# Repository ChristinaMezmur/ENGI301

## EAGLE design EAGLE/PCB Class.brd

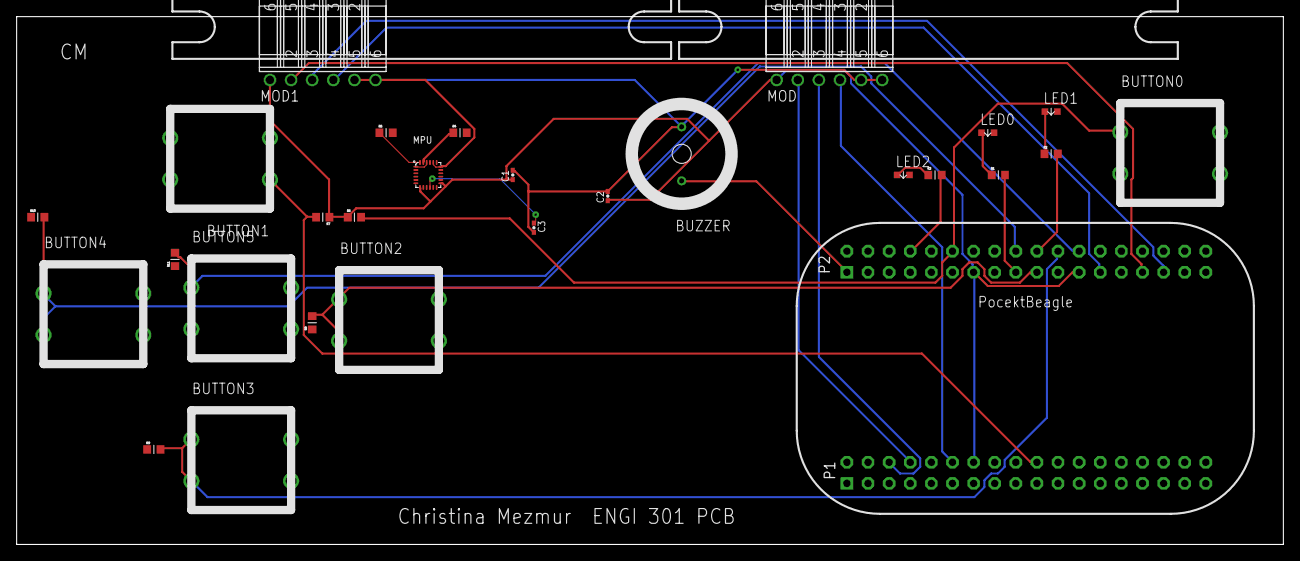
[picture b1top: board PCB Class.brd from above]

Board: 4 copper layers, 152.4 x 63.5 mm, 32 parts (0 on the bottom side), 30 nets.

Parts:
BUTTON0, BUTTON1, BUTTON2, BUTTON3, BUTTON4, BUTTON5: BUTTON
BUZZER: SEM-1203(42)
C1: 10nF; C0402
C2, C3: 0.1uF; C0402
LED0, LED1, LED2: LTST-C191TBKT
MOD, MOD1: MOD-LED8X8RGB-CONN; FE06W
MPU: QFN-3MMX3MM
POCKETBEAGLE: POCKETBEAGLE
R1, R2, R3: 1K; R0603
R4, R5, R6, R7, R8, R9, R10, R11: 3K; R0603
U$1, U$2, U$3, U$4: MOD-LED8X8RGB

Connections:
8X8CLK: MOD.2, POCKETBEAGLE.8
8X8CLK1: MOD1.2, POCKETBEAGLE.65
8X8CS: MOD.3, POCKETBEAGLE.6
8X8CS1: MOD1.3, POCKETBEAGLE.67
8X8MOSI: MOD.4, POCKETBEAGLE.12
8X8MOSI1: MOD1.4, POCKETBEAGLE.61
BUTTON0: BUTTON0.P$1, BUTTON0.P$3, POCKETBEAGLE.48, R6.2
BUTTON1: BUTTON1.P$1, BUTTON1.P$3, POCKETBEAGLE.20, R7.2
BUTTON2: BUTTON2.P$1, BUTTON2.P$3, POCKETBEAGLE.55, R8.2
BUTTON3: BUTTON3.P$1, BUTTON3.P$3, POCKETBEAGLE.58, R9.2
BUTTON4: BUTTON4.P$1, BUTTON4.P$3, POCKETBEAGLE.54, R10.2
BUTTON5: BUTTON5.P$1, BUTTON5.P$3, POCKETBEAGLE.60, R11.2
GND: BUZZER.P$2, C1.2, C2.2, C3.2, MOD.5, MOD.6, MOD1.5, MOD1.6, MPU.18, MPU.20
unnamed: C3.1, MPU.10
unnamed: MPU.24, R5.1
unnamed: MPU.23, R4.1
unnamed: POCKETBEAGLE.56, R2.2
unnamed: POCKETBEAGLE.44, R3.2
unnamed: MPU.1, MPU.22
unnamed: LED2.P$1, R3.1
unnamed: LED0.P$1, R1.1
unnamed: LED1.P$1, R2.1
unnamed: POCKETBEAGLE.53, R1.2
unnamed: BUZZER.P$1, POCKETBEAGLE.37
unnamed: BUTTON0.P$2, BUTTON0.P$4
unnamed: BUTTON1.P$2, BUTTON1.P$4
unnamed: BUTTON5.P$2, BUTTON5.P$4
unnamed: BUTTON3.P$2, BUTTON3.P$4
unnamed: BUTTON2.P$2, BUTTON2.P$4
SYS_VDD1_3P3V: C1.1, C2.1, MOD.1, MOD1.1, MPU.8, MPU.13, POCKETBEAGLE.14, POCKETBEAGLE.49, POCKETBEAGLE.59, R6.1, R7.1

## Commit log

2018-04-11 Initial checkin of schematics / layout
2018-04-16 COMMIT2
2018-04-16 Updates to schematics
2018-04-20 Commit#idk
2018-04-20 FINAL PROJECT 2A MEZMUR
2018-04-20 ACTUAL FINAL PROJECT 2a Mezmur
